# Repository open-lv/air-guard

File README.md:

# Air Guard 💨

Air Guard is a do-it-yourself electronics kit for building an **air quality monitor** for your school, home or office.

## Project Goals

Create a kit of electronics components, software tools and instructions for kids (and anyone) to create air quality monitors for their living spaces using affordable and readily available components and friendly programming tools.

## Design Goals

- Use existing electronics modules for all components to ensure the parts are available and affordable.

- Build on the experience of other electronics platforms such as [micro:bit](https://microbit.org), [M5Stack](https://m5stack.com), [MicroPython](https://micropython.org), [ESPHome](https://esphome.io) which provide user-friendly tools and concepts for exploring the hardware and software features.

- Allow space for customization and creative expression to encourage use and ownership of the devices.

- Let users experience quick wins early to encourage continued exploration.

- Design for groups of people building the kit and splitting responsibilities.

## Technical Design

- Rely on permanent power supply over USB to avoid limiting the available sensor components (due to their power consumption) and to encourage creative expression in software through the use of LEDs, buzzers and displays. See [issue #4](https://github.com/open-lv/air-guard/issues/4) for the discussion around energy usage.

- Use [MicroPython](https://micropython.org) as the software platform due to the available tooling and accessible programming environments. See [issue #6](https://github.com/open-lv/air-guard/issues/6) for discussion.

- Use ESP32 based microcontrollers due to extensive support for MicroPython and the selected sensor components, and affordable development kits. See [issue #7](https://github.com/open-lv/air-guard/issues/7) for the suggested bill of materials.

## Contribute

Join our [chat on Gitter](https://gitter.im/open-lv/air-guard) to discuss ways to contribute. Issues and pull requests are always welcome!

## Credits

Created [by contributors](https://github.com/open-lv/air-pilot/graphs/contributors).

## License

This is an open source project where the [software](software) and [documentation](docs) are licensed under [MIT](LICENSE) while [the hardware](hardware) is licensed under [CC BY-NC-SA 4.0](hardware/LICENSE).

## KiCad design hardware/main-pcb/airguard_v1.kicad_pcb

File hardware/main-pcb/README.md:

# GAISA SARGS R03

Version 3 hardware, designed in Kicad 5
by 
SKRUBIS & ZAHARS ZE

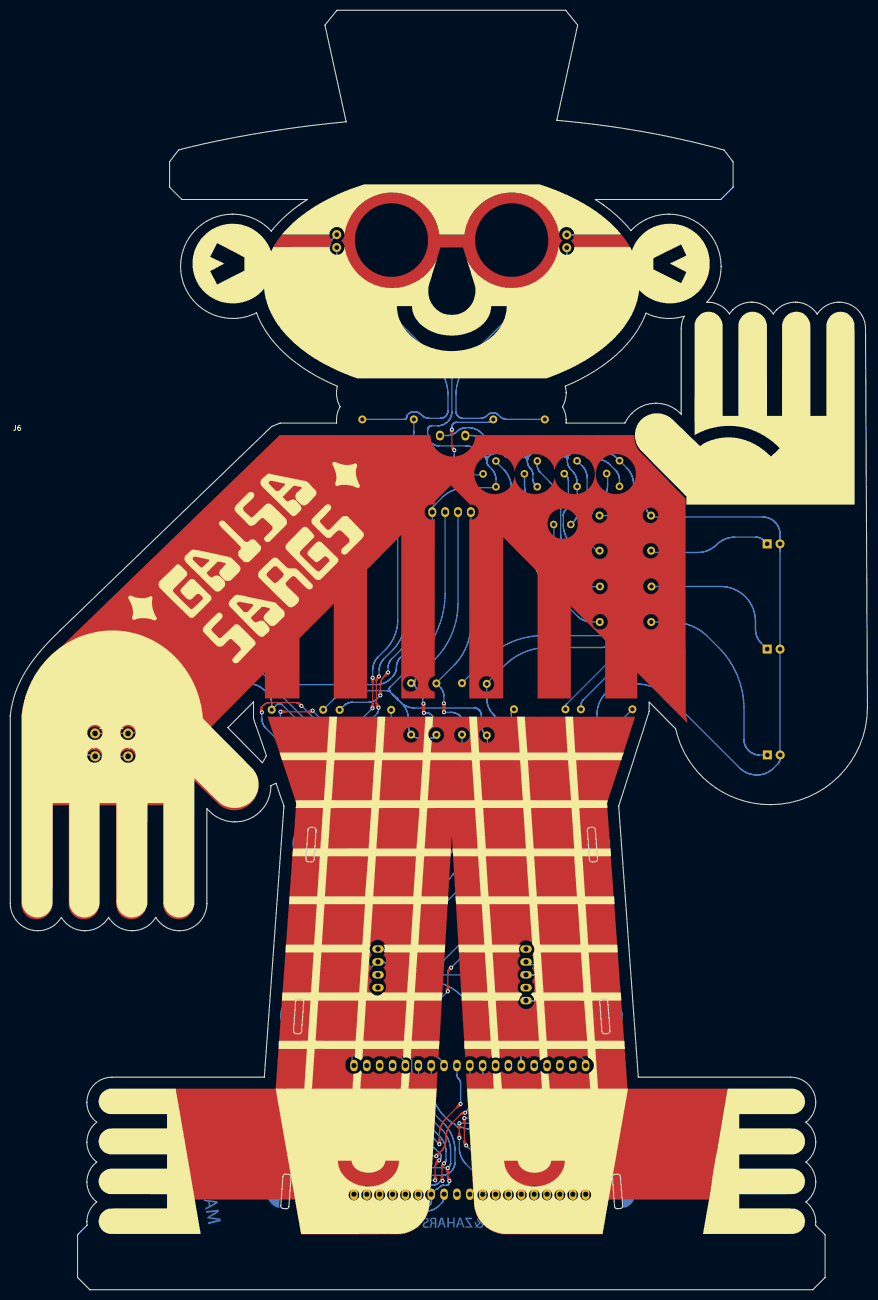
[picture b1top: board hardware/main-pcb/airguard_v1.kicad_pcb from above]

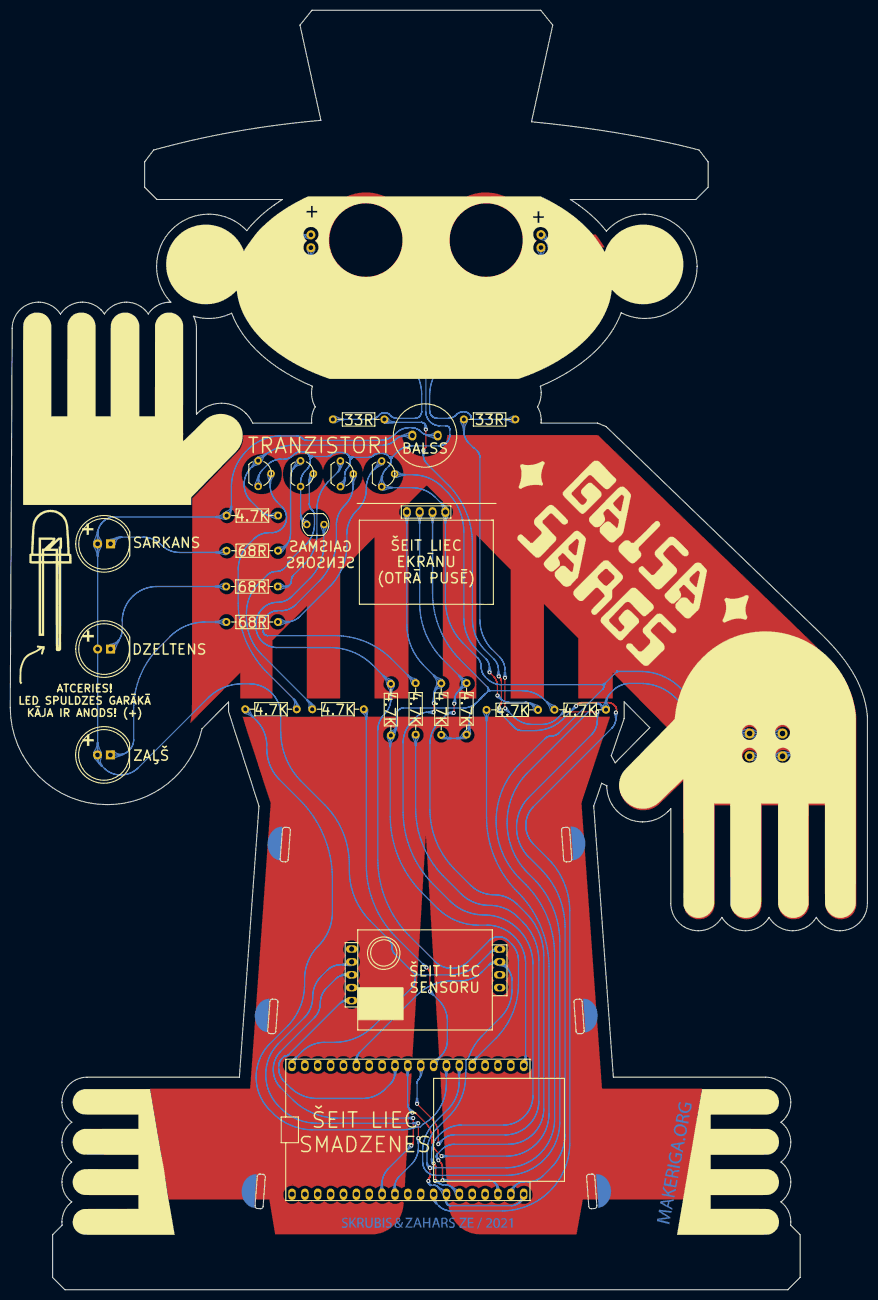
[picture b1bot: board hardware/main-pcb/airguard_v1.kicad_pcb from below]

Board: 2 copper layers, 169.1 x 252.5 mm, 35 parts (22 on the bottom side), 29 nets.

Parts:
BZ1: BALSS; buzzer-C360606
D1, D2: LED; LED_D3.0mm
DZELTENS: LED_YELLOW; LED_D10.0mm
J1, J3, J6: Conn_01x04_Female; Dummy_Empty
J4, J5: Conn_01x19_Female; Dummy_Empty
Q1, Q2, Q3, Q4: PN2222A; TO-92_Molded_Wide
R1, R2, R3, R4, R6, R7, R8, R9, R10: 4.7K; R_Axial_DIN0207_L6.3mm_D2.5mm_P10.16mm_Horizontal
R5: R_PHOTO 8-20kR; Resistor_LDR_5.1x4.3_RM3.4
R11, R12, R13: 68R; R_Axial_DIN0207_L6.3mm_D2.5mm_P10.16mm_Horizontal
R14, R15: 33R; R_Axial_DIN0207_L6.3mm_D2.5mm_P10.16mm_Horizontal
SARKANS: LED_RED; LED_D10.0mm
SW1: SW_Push; SW_PUSH_6mm_h5mm
U1: MH-Z19B; Winsen_MH-Z19B
U2: ESP32_DEVKIT_C
U3: EKRĀNS; SSD1306
ZAĻŠ: LED_GREEN; LED_D10.0mm
e: Val**; 02

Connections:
+3V3: R1.1, R2.1, R4.2, R7.2, U2.1, U3.2
+5V: BZ1.1, DZELTENS.2, R6.2, SARKANS.2, U1.6, U2.19, ZAĻŠ.2
BEEP: R3.2, U2.7
BUTTON: R7.1, SW1.1, U2.6
CAL: U1.5, U2.11
GND: D1.1, D2.1, Q1.1, Q2.1, Q3.1, Q4.1, R5.2, SW1.2, U1.7, U2.14, U2.32, U2.38, U3.1
GREEN: R10.2, U2.10
LIGHT: R4.1, R5.1, U2.5
L_EYE: R15.2, U2.37
unnamed: BZ1.2, Q1.3, R6.1
unnamed: D1.2, R14.1
unnamed: D2.2, R15.1
unnamed: DZELTENS.1, R12.2
unnamed: Q1.2, R3.1
unnamed: Q2.2, R8.1
unnamed: Q2.3, R11.1
unnamed: Q3.2, R9.1
unnamed: Q3.3, R12.1
unnamed: Q4.2, R10.1
unnamed: Q4.3, R13.1
unnamed: R11.2, SARKANS.1
unnamed: R13.2, ZAĻŠ.1
RED: R8.2, U2.8
RXD2: U1.3, U2.27
R_EYE: R14.2, U2.31
SCL: R1.2, U2.36, U3.3
SDA: R2.2, U2.33, U3.4
TXD2: U1.2, U2.28
YELLOW: R9.2, U2.9

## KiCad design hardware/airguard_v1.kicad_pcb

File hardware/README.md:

# GAISA SARGS Hardware

GAISA SARGS is an open source air quality monitor DIY kit for kids & teenagers.

Current revision: **03**

Known bugs: **none yet**

Authors: **Skrubis & Zahars Ze**

The project consists of 3 PCBs you need to order:
1) [The main PCB x1 ](https://github.com/open-lv/air-guard/tree/main/hardware/main-pcb) 
2) [The side PCB x2 ](https://github.com/open-lv/air-guard/tree/main/hardware/side-pcb)
3) [The rear PCB x1 ](https://github.com/open-lv/air-guard/tree/main/hardware/rear-pcb)

If you want to practice soldering, feel free to order some "friend" PCBs:
[DRAUGS PCB ](https://github.com/open-lv/air-guard/tree/main/hardware/draugs-pcb)

The PCBs are drawn in Kicad 5.1.x
The schematic of the main board: [airguard_v1.pdf](https://github.com/open-lv/air-guard/blob/main/hardware/main-pcb/airguard_v1.pdf)

All boards are your run of the mill pcbhouse 
(OSH, pcbway, jlcpcb, etc.) standard process compatible. 

Just upload the Gerber ZIP file and choose the options specified below:

Layers: 2

Thicness: 1.6mm

Soldermask color: Blue 
(as intended by the artist Zahars Ze, however we invite you to experiment and show us the results)

Surface finish: RoHS HASL
if used by kids; show us how it looks in ENIG, if you ever make one

The DIY kit BOM can be viewed in the BOM folder, however at this time it is very preliminary in nature. 
Most likely not much will change, but please keep it in mind while viewing it.

**The simple BOM is as follows**:
1) Main PCB - x1
2) Side PCB - x2
3) Rear PCB - x1
4) 19pin 2.54mm female header - x2
5) ESP-32 DevkitC V4 or older version (check pinouts in the main pcb schematic) - x1
6) 4pin 2.54mm female header - x1
7) 5pin 2.54mm female header - x1
8) Winsen MHZ19-C (or -B) - x1
9) 4.7k TH Resistor - x9
10) 2N2222 NPN transistor TO-92 or similar - x4
11) 10mm TH LED Green - 1x
12) 10mm TH LED Red - 1x
13) 10mm TH LED Orange(Yellow) - 1x
14) 3mm TH LED White - 2x
15) 68R TH Resistor - 3x
16) 33R TH Resistor - 2x
17) Buzzer 10mm pin to pin - 1x
18) Standard TH push button 6mm - 1x
19) SSD1306 based I2C OLED 0.96" 128x64px - 1x - check voltage and pinout on the pcb!!
20) 220uF electrolytic capacitor(6.3x11, 25+V)

That's it! It's a very simple project electroncis wise, so feel free to experiment, customize or improve it!

This portion of the project is licensed under [CC BY-NC-SA 4.0](hardware/LICENSE).

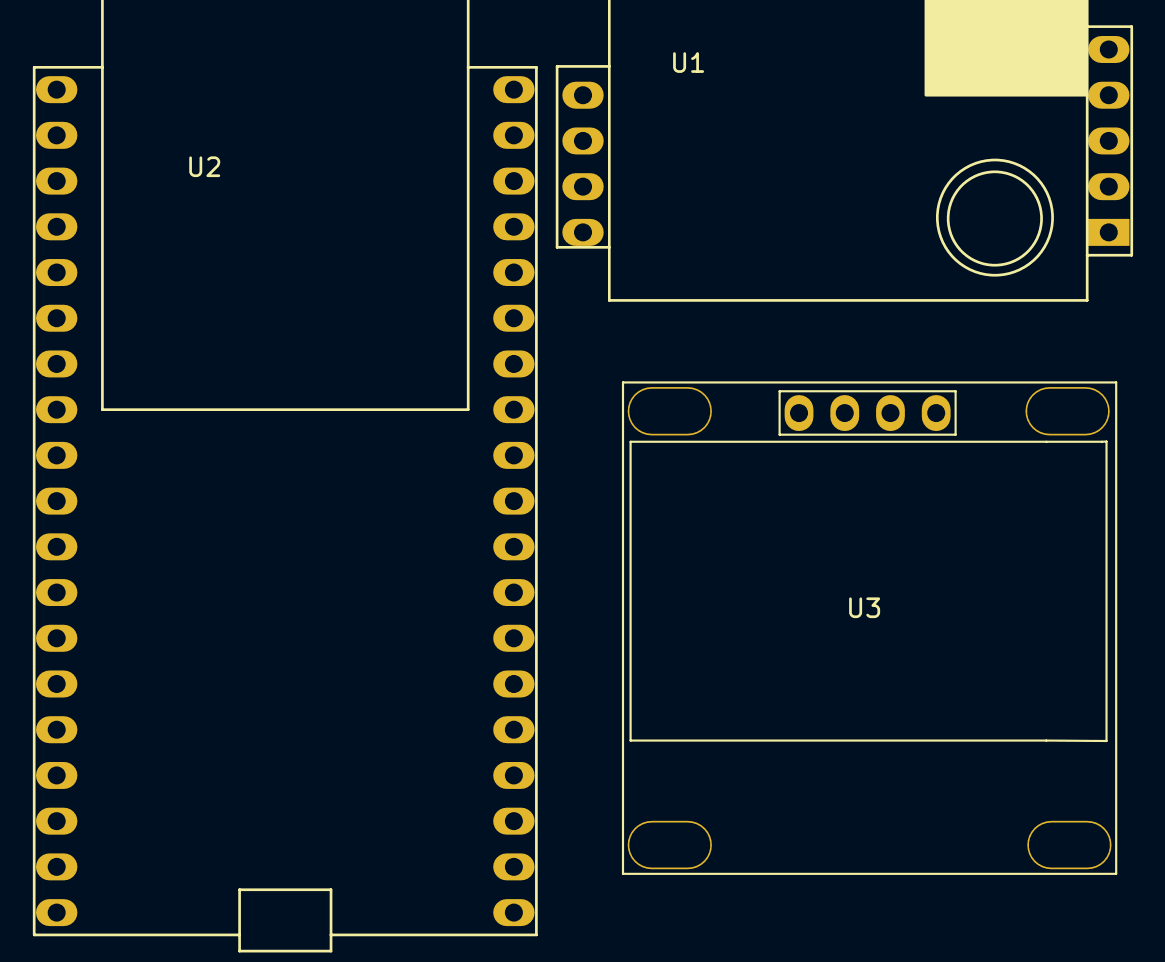
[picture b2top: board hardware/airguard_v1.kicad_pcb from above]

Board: 2 copper layers, 3 parts (0 on the bottom side), 2 nets, no tracks yet.

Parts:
U1: MH-Z19B; Winsen_MH-Z19B
U2: ESP32_DEVKIT_C
U3: SSD1306

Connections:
+5V: U1.6, U2.19
GND: U1.7, U2.14, U2.18, U2.32, U2.38

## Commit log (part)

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2021-09-23 Create LICENSE
2021-09-23 Add readme
2021-09-23 Rename to air guard, add illustration
2021-09-23 Ignore system files
2021-09-23 Set theme jekyll-theme-architect
2021-09-23 Add Gitter badge
2021-09-23 Add chat button
2021-09-23 Add contribute section
2021-09-24 Explain the design goals
2021-09-26 Split out project goals
2021-09-26 Define the technical design
2021-09-27 Adding skeleton for project hardware v1
2021-09-27 Adding datasheets to the components used
2021-09-27 Adding KiCad .gitignore to the hardware folder
2021-09-27 Replacing MH-Z19B with one from https://gitlab.com/IT-Berater/twco2sensor-mh-z19b and adding a symbol library from there
2021-09-27 Adding ESP32 DEVKIT C library and footprint files - just designed from scratch according to datasheets, feel free to reverify
2021-09-27 Foolproofing the MH-Z19B footprint - enlarging pads and adding soldermask to top so that they can't be soldered incorrectly
2021-09-27 Adding new symbols to the schematic and PCB - no other work done
2021-09-27 Updating README a bit
2021-09-27 Adding 3D models for the OLED, CO2 sensor and ESP32 board
2021-09-27 Adding the OLED and all 3d models; connecting some of the signals to the corresponding ESP32 pins
2021-09-27 Adding more references to sources to the README
2021-09-28 Sanity check - 0.8mm drills weren't enough for the footprints I used, switched them to 1mm drills instead
2021-10-15 Add the firmware
2021-10-15 We might need software for generic software at some point so be explicit about this being the firmware
2021-11-24 Create CNAME
2021-12-07 added basic platformio sketch with actual pinouts for hw 0.1 and 0.2
2021-12-07 added HW 0.2
2021-12-08 Remove the legacy banner
2021-12-08 Link to both licenses
2021-12-08 Remove the GitHub pages hosting
2021-12-18 added very drafty Bill Of Materials
2021-12-20 Add automated GH action releases for gerber zips
2021-12-22 updated readme.md, added schematic pdf
2021-12-25 removed drug baggies for PC ppl
2021-12-28 Izslēdzam kalibrāciju, jo tā ir akurāta tikai ārtelpās
2022-01-08 Refs #10: Initial, barely working MicroPython firmware
2022-01-08 Refs #10: Fix incorrect checksum calculation for packets with checksums of 0x00
2022-01-10 uPy: Refactor main thread into separate functions, fix unhandled WiFi exceptions (e.g. network not found)
2022-01-10 uPy: Implement publishing the data to ThingSpeak channel via MQTT
2022-01-10 Add the basic flasher
2022-01-10 Add the docker environment
2022-01-10 Define the defaults
2022-01-10 uPy: fix trivial but important issues caught by pycharm (inconsistent indentation, missing attributes)
2022-01-10 Use the default esptool.py environment variable
2022-01-10 uPy: refactor screen drawing in a separate class to allow easier implementation of multiple screen states
2022-01-10 Add a basic readme
2022-01-10 This is more than just a generic flasher
2022-01-10 Match the port
2022-01-10 Match the expected port env name
2022-01-10 Focus on local tooling
2022-01-10 Pass the port environment variable along
2022-01-10 Ignore local overrides
2022-01-10 Introduce the device ID helper
2022-01-10 Log to a file
2022-01-10 Ignore flashed device list
2022-01-10 Deal with each file
2022-01-11 Add chip to flash erasing
2022-01-11 Change test to resolve SC1072 issue
2022-01-11 uPy: implement manual calibration request via button press/confirmation on screen
2022-01-11 uPy: document the manual calibration process
2022-01-11 uPy: Attempt at swallowing less exceptions in sargs.py
2022-01-12 Refactored flashing utility to use mpremote and improved UX
2022-01-12 Fixed bug in device auto-detection
2022-01-12 uPy: three long beeps for high CO2 level
2022-01-14 uPy: Detect warming up of MHZ19C
    The detection is bbased on it starting to report a different value after
    turning on.
2022-01-14 uPy: disable ABC calibration by default
2022-01-14 uPy: fix blinking of R/G/B status LEDs due to context switching
    Previously the code in main.py turned off all LEDs and then turned on
    the needed one based on sensor readings. However, if execution context
    is switched to background thread after LEDs have been turned off, but
    before the new one was turned on, and the operation in background
    thread was time-consuming (WiFi re-association, publishing to mqtt)
    visible blinking of the LED could be observed.
2022-01-14 uPy: improve warmup detection by introducing minimal warmup time
2022-01-14 uPy: optional temp. reporting via mqtt, improved sensor status report
    During warmup, LCD does not congratulate you on having fresh air
2022-01-20 updated main board to R3
2022-01-20 plot sch
2022-01-20 cleanup rear gerber folder
2022-01-20 added draugs pcb
2022-01-20 draugs pcb img
2022-01-20 updated side pcb to have cutout for weird devkitc interpretations
2022-01-25 tools/flasher: migrate to micropython v1.18, fix flashing process
    flash.sh:
    * ignore empty build dir (failed with non-existant filename)
    * add build dir to .gitignore
    * mpremote created a build folder on device and copied files there
2022-01-25 Adding exec permissions to flash.sh
2022-01-26 Added .idea to .gitignore
2022-01-26 uPy: Added Tinyweb module
2022-01-26 uPy: Introduced main.py event loop
2022-01-26 uPy: Added portal server and stub index.html
2022-01-26 uPy: Added static files to flasher copy
2022-01-29 Define the calibration service
2022-01-29 Add an ID for the whole sensor item
2022-02-03 added sponsor logos -mask only-
2022-02-05 fixed dash in rear pcb, fixed nsa logo gerber archive
2022-02-06 uPy Portal: Added Vue.js sample app
2022-02-06 uPy Portal: Added `min` sources and upload only gz sources
2022-02-07 uPy Portal: Added Rest APIs for Sargs
2022-02-08 uPy Stubs: Added uPy 18 stubs to project
2022-02-09 uPy: Introduce event loop to Sargs
2022-02-09 uPy Flasher: Restoring flash erasing to flash.sh
2022-02-09 uPy Sargs: Returning buzzer functionality
2022-02-09 uPy Sargs: Refactoring asyncio and package usages
2022-02-10 uPy Flasher: Added fw autodownload from `open-lv/micropython` releases
    https://github.com/open-lv/micropython/releases/latest
2022-02-11 uPy Flasher: Change firmware binary
2022-02-11 uPy Portal: Default `/` page fix
2022-02-11 mPy: migrate from pythonic ssd1306 driver to display module from badge.team
2022-02-12 mPy: add animated startup/intro/main/open-window screens
2022-02-15 uPy Flasher: Fix empty build dir errors
2022-02-15 moved BOM to HW, removed non relevant spreadsheets
2022-02-15 mPy: remove files that are frozen, copy assets in flash.sh
    See open-lv/micropython/ports/esp32/boards/AIRGUARD/modules for the
    source code of removed python files.
2022-02-15 uPy: Move frozen scripts to stubs
2022-02-15 uPy: Async all UI draws
2022-02-15 uPy: Fix async buzzer calls
2022-02-15 uPy: Remove blocking `sleep` calls
2022-02-16 main screen added degree symbol, moved PPM asset to PNG asset, repositioned elements
2022-02-16 updated warmup with beating heart
2022-02-16 made splash logo longer
2022-02-16 sveika pasaule -> versija
2022-02-16 added more PPM pngs
2022-02-16 added cloud icons
2022-02-17 added large heart anims and another screen draft to ui
2022-02-17 EKG made faster
2022-02-17 Make it cross-platform
2022-02-17 Minify assets
2022-02-17 Extract and store the selected port by path instead of the full info string
2022-02-17 mPy: draw degree symbol in the correct place, based on width of displayed value
2022-02-17 mPy: use git tag as version
2022-02-17 flash.sh: reboot device after flashing
2022-02-17 mPy: display first 8 chars of version string on boot
2022-02-17 mPy: remove uart selection as I now have the same hw as kit
2022-02-17 flash.sh: don't overwrite the file containing flashed devices, register firmware versions as well
2022-02-17 mPy: change main screen to large beating heart, add screen switching
2022-02-17 removed empty files/folders
2022-02-17 added credits assets
2022-02-17 Facelift portal UI
2022-02-17 Do not wait for stations to load before showing page
    Add SSID to wifi state response
    Add mock method for internet connections check
2022-02-18 fixed readme
2022-02-18 created folder for current gerbers
2022-02-18 added gerber folder readme
2022-02-18 added gerber folder readme vendors
2022-02-18 add rear pcb readme
2022-02-18 added known bugs for rear pcb
2022-02-18 add side pcb readme
2022-02-18 mPy: add credits
2022-02-18 mPy: speed up everything, invert eye functionality, fix heartbeat arrhythmia
2022-02-19 Added Maris to credits
2022-02-19 uPy Stubs: Update `uasyncio` stubs
2022-02-19 uPy Stubs: Added captive DNS server to stubs
2022-02-19 uPy Portal: Added captive http server handling
2022-02-21 uPy Stubs: Added network_manager to frozen modules
2022-02-21 uPy Stubs: Enable AP mode if no SSID provided
2022-02-21 uPy Stubs: network_manager: Reset service only if once connected
2022-02-21 uPy Portal: Added captive portal capabilities
2022-02-25 uPy: Added default values for config variables
2022-02-28 Always specify the serial port for mpremote commands
2022-02-28 mPy: center CO2 sensor failed message
2022-02-28 mPy: fix LCD, CO2 sensor error handling
2022-02-28 Lessless minify
2022-02-28 uPy Stubs: tinyweb: Add buffer size option to tinyweb responses
2022-02-28 mPy: add plot screens
2022-02-28 uPy Portal: Increase buffer size to 512
2022-02-28 uPy Screen: Redraw screens with bigger delay
2022-02-28 uPy Screen: Add `await` to unblock event loop
2022-03-01 uPy: Async plot drawer
2022-03-01 Introduce our own implementation
2022-03-01 Match naming convention with the rest
2022-03-01 Let the logger to the sprintf
2022-03-01 Use the machine ID for now
2022-03-01 Send the version too
2022-03-06 uPy: Fix missing measurement state update
2022-03-06 uPy Portal: Addressed FCP to be visualized ASAP
2022-03-07 uPy: Moved config to JSON format
2022-03-07 uPy: Added possibility to save configuration to JSON file
2022-03-07 uPy Portal: Added endpoint for wifi settings save
2022-03-07 uPy Portal: Fix typo
2022-03-07 uPy Portal: Add input validation to WIFI settings
2022-03-07 Add confirm message upon saving Wifi settings
    Send Wifi settings to correct end-point
2022-03-07 uPy: Changed await timeout from 1 to 0 for unblocking purposes
2022-03-07 uPy: add async possibility to mhz19 driver
2022-03-08 uPy: Added asyncio metrics
2022-03-08 uPy: GH action for software release
2022-03-09 uPy: Added back portal
2022-03-09 uPy NetworkManager: Events not triggered if WIFI connected before NM
2022-03-09 uPy: add network status screen
2022-03-09 uPy Release: Remove archive zipping
2022-03-13 MAC-generated personalized beeping/chirps/nice sounds/etc
2022-03-13 uPy: OTA
2022-03-13 uPy Stubs: Added `utarfile`
2022-03-13 uPy OTA: Added OTA portal handle
    uPy Flasher: Extracting build version to flasher
2022-03-13 uPy Flasher: Airguard versioning
2022-03-13 uPy OTA: Remove all nonoriginal versions upon OTA
2022-03-13 uPy OTA: Fix incorrect function reference
2022-03-13 uPy OTA: Fix installer issues
2022-03-13 uPy: Fix versioning display
2022-03-13 uPy OTA: Fix other version removal function
2022-03-14 uPy Portal: Increase response buffer size to 512 bytes
2022-03-15 uPy OTA: Remove threading in favour of thread safety
2022-03-15 uPy OTA: Fix reset stage `remove other versions`
2022-03-15 uPy Portal: Add version information to state endpoint
2022-03-15 uPy: Add update prompt on screen if new version is available
2022-03-15 uPy: fix ota prompt timeout in sargsui
2022-03-16 Add release list to protal
    Add update to lates button to release list
    Show new version badge in navigation
2022-03-17 In flash.sh, changing 'esptool run' to 'mpremote reset' to work around a probably-local-software-stack bug
2022-03-20 uPy Flasher: Hard machine reset on complete flash
2022-03-20 uPy IOT: Extracted MQTT implementation to separate module
2022-03-20 uPy Flasher: Added label printing capabilities
2022-03-20 uPy Portal: Typo fix
2022-03-20 Add full tar of release alongside smaller archive
2022-03-20 uPy Flasher: Separate provisioning script
2022-03-21 added printed manual
2022-03-21 cleanup
2022-03-21 readme
2022-03-22 soldering card
